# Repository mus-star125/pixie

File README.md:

# pixie

## What is Pixie?

Pixie is a LED circuit PCB project created as part of Hack Club's Half Life program.

My original idea was to create a small interactive OLED pet, but due to time constraints and challenges with circuit design, I decided to simplify the project into a basic LED circuit.

This project helped me practise the fundamentals of electronic circuit design and PCB layout using KiCad.

## How It Works

The circuit uses a simple LED, a resistor, and a screw terminal.

- **LED:** Produces light when current flows through it.
- **Resistor:** Limits the current flowing through the LED to help protect it.
- **Screw Terminal:** Provides a connection point for the power supply.

## Components

| Component | Quantity | Purpose |
|---|---:|---|
| LED | 1 | Produces light |
| Resistor | 1 | Limits current |
| Screw terminal | 1 | Connects the power supply |
| PCB | 1 | the base|

## Design Process

I designed the circuit schematic and PCB layout using KiCad.

I learnt
- Creating electronic schematics.
- Selecting component footprints.
- Placing components on a PCB.
- Routing copper traces.
- Running ERC and DRC checks.
- Generating Gerber and drill files.

## Inspiration & Resources

I used a YouTube tutorial as a reference for learning how to create this basic LED circuit.

Tutorial: (https://www.youtube.com/watch?v=PJ5DdO47Wx0)

I would like to revisit my original interactive OLED pet idea in the future, using what I learned from this project to build a more complex circuit.

---

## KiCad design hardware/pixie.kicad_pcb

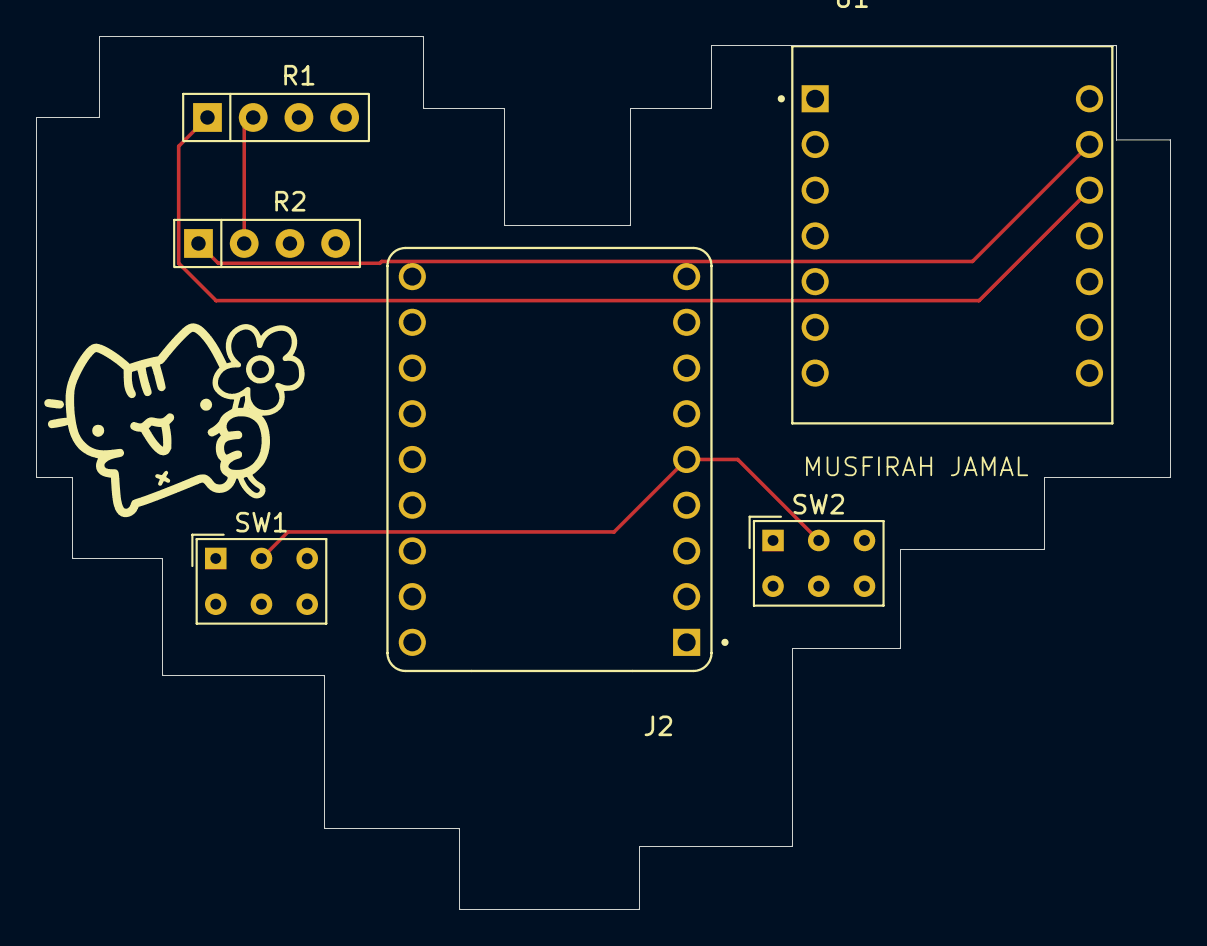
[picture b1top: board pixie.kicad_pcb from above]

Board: 2 copper layers, 63.0 x 48.5 mm, 6 parts (0 on the bottom side), 4 nets.

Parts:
J2: Conn_01x04; Waveshare ESP32-S3-Zero
R1: R_Photo; R_Array_SIP4
R2: 10K; R_Array_SIP4
SW1, SW2: SW_Push; SW_NKK_GW12LJP
U1: XIAO-ESP32-C3-SMD; XIAO ESP32-S3

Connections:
/D3: R1.2, R2.2
GND: J2.2, SW1.2, SW2.2
unnamed: R2.1, U1.13 (GND)
unnamed: R1.1, U1.12 (3V3_OUT)

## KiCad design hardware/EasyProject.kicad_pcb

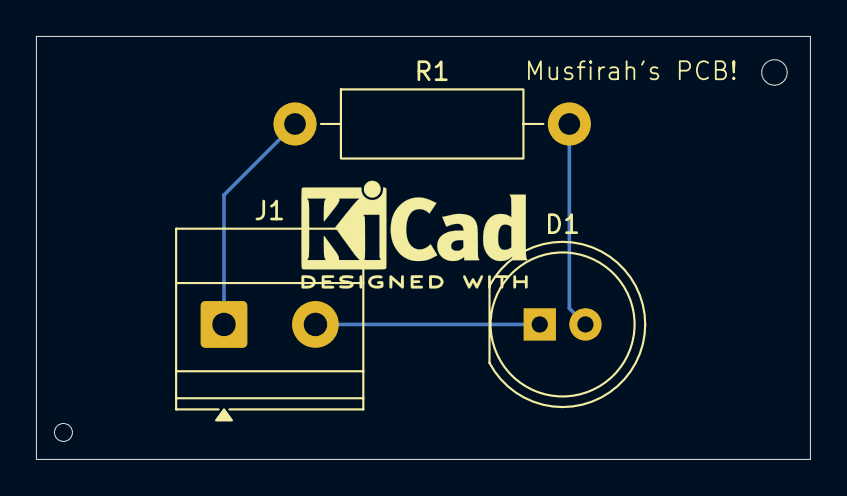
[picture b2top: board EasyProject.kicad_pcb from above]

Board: 2 copper layers, 43.0 x 23.5 mm, 3 parts (0 on the bottom side), 3 nets.

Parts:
D1: LED; LED_D8.0mm
J1: Screw_Terminal_01x02; TerminalBlock_Phoenix_MKDS-1,5-2-5.08_1x02_P5.08mm_Horizont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
R1: R; R_Axial_DIN0411_L9.9mm_D3.6mm_P15.24mm_Horizontal

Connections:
GND: D1.1 (K), J1.2
unnamed: D1.2 (A), R1.2
unnamed: J1.1, R1.1
